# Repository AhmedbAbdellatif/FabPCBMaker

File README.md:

# FabPCBMaker
A fabbable, cheap, light and small CNC for PCBs

## Project Development
I developed this project as a final project for FabAcademy 2017. My idea was to make it possible to make a CNC mill for PCBs in a FabLab at an as low as possible cost (less than 100€). 
In this page I will be providing Information on how to replicate this along with the design files required  

## Specifications
* 100x160x50mm working area
* 0.0025mm theorethical resolution (0.04mm realistic)
* 18mm plywood cnc milled frame
* POM bearing and motor holder
* brushless spindle motor
* 3 x Pololu A4988
* 3 x Nema 17 threaded rod stepper motors
* 8mm linear rods
* satshakit board

## Thanks 
Daniele Ingrassia<br />
[Satshakit](https://github.com/satshakit)<br />

[FabLab Kamp-Lintfort](http://fablab.hochschule-rhein-waal.de/index.php/en/)<br />
[Hochschule Rhein-Waal](https://www.hochschule-rhein-waal.de/en)<br />
Friedrich-Heinrich-Allee 25, 47475 Kamp-Lintfort, Germany
fablab@hochschule-rhein-waal.de
## License
This work is licensed under the terms of Attribution-NonCommercial-ShareAlike 4.0 International ([CC BY-NC-SA 4.0](https://creativecommons.org/licenses/by-nc-sa/4.0/))

## Authors  
Ahmed B.Abdellatif<br />
Student Assistant at FabLab Kamp-Lintfort<br />
Communication and Information Engineering student Hochschule Rhein-Waal<br />

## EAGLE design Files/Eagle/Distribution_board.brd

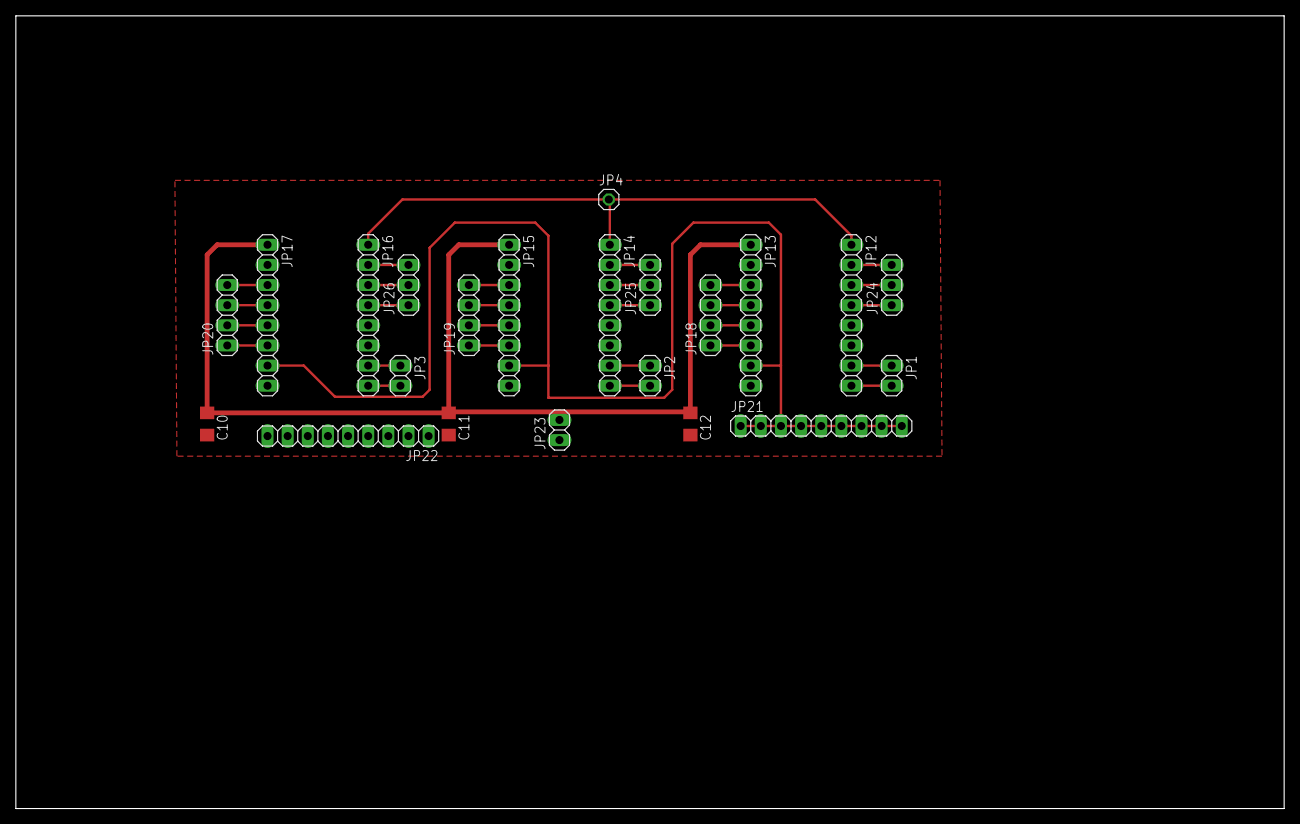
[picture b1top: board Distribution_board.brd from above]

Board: 2 copper layers, 160.0 x 100.0 mm, 22 parts (0 on the bottom side), 31 nets.

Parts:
C10, C11, C12: 100uF; C1206
JP1, JP2, JP3: 1X02
JP4: 1X01
JP12: X1; 1X08
JP13: X2; 1X08
JP14: Y1; 1X08
JP15: Y2; 1X08
JP16: Z1; 1X08
JP17: Z2; 1X08
JP18: Xout; 1X04
JP19: Yout; 1X04
JP20: Zout; 1X04
JP21, JP22: 1X09
JP23: MotorPW; 1X02
JP24, JP25, JP26: 1X03

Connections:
ENABLE: JP4.1, JP12.1, JP14.1, JP16.1
GND: C10.2, C11.2, C12.2, JP13.2, JP13.8, JP15.2, JP15.8, JP17.2, JP17.8, JP22.1, JP22.2, JP22.3, JP22.4, JP22.5, JP22.6, JP22.7, JP22.8, JP22.9, JP23.1
unnamed: JP17.3, JP20.4
unnamed: JP17.4, JP20.3
unnamed: JP17.5, JP20.2
unnamed: JP17.6, JP20.1
unnamed: JP15.6, JP19.1
unnamed: JP15.5, JP19.2
unnamed: JP15.4, JP19.3
unnamed: JP15.3, JP19.4
unnamed: JP13.3, JP18.4
unnamed: JP13.4, JP18.3
unnamed: JP13.5, JP18.2
unnamed: JP13.6, JP18.1
unnamed: JP12.2, JP24.3
unnamed: JP12.3, JP24.2
unnamed: JP12.4, JP24.1
unnamed: JP14.2, JP25.3
unnamed: JP14.3, JP25.2
unnamed: JP14.4, JP25.1
unnamed: JP16.2, JP26.3
unnamed: JP16.3, JP26.2
unnamed: JP16.4, JP26.1
VCC: JP13.7, JP15.7, JP17.7, JP21.1, JP21.2, JP21.3, JP21.4, JP21.5, JP21.6, JP21.7, JP21.8, JP21.9
VMOT: C10.1, C11.1, C12.1, JP13.1, JP15.1, JP17.1, JP23.2
XDIR: JP1.2, JP12.8
XSTEP: JP1.1, JP12.7
YDIR: JP2.2, JP14.8
YSTEP: JP2.1, JP14.7
ZDIR: JP3.2, JP16.8
ZSTEP: JP3.1, JP16.7

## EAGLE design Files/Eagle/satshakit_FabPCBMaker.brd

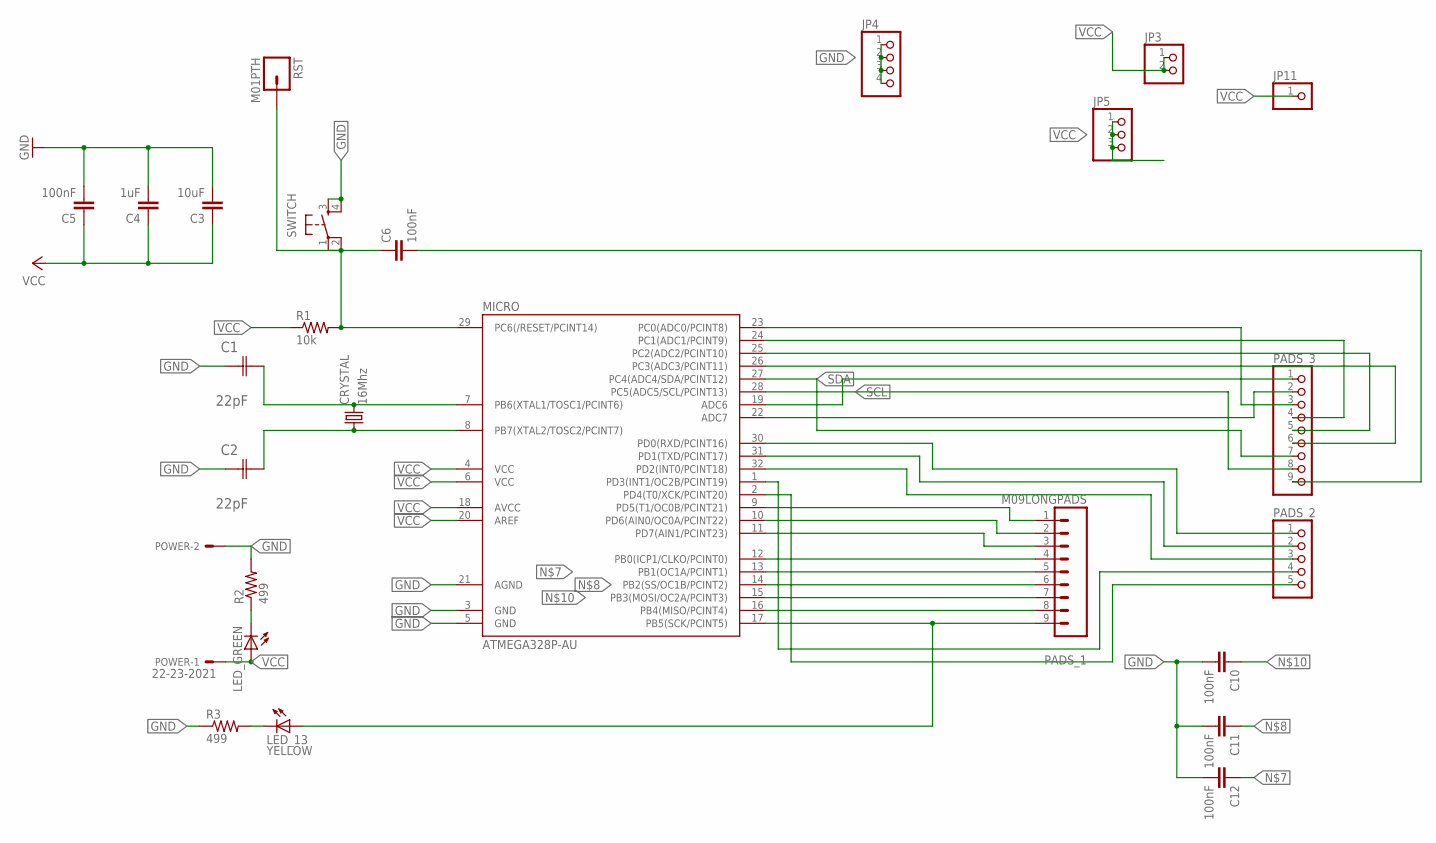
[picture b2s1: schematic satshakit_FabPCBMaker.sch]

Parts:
C1, C2: 22pF; CAPC3216X178N
C3: 10uF; 1206
C4: 1uF; 1206
C5, C6, C10, C11, C12: 100nF; 1206
CRYSTAL: 16Mhz; CSM-7X-DU
JP3: PINHD-1X2; 1X02
JP4: PINHD-1X4; 1X04
JP5: PINHD-1X3; 1X03
JP11: PINHD-1X1; 1X01
LED_13: YELLOW; 1206
LED_GREEN: LED1206; 1206
MICRO: ATMEGA328P-AU; TQFP32-08
PADS_1: M09LONGPADS; 1X09_LONGPADS
PADS_2: PINHD-1X5; 1X05
PADS_3: PINHD-1X9; 1X09
POWER: 22-23-2021
R1: 10k; 1206
R2, R3: 499; 1206
RST: M01PTH; 1X01
SWITCH: 6MM_SWITCH6MM_SWITCH; 6MM_SWITCH

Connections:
GND: C1.1 (C1), C2.1 (C1), C3.2, C4.2, C5.2, C10.2, C11.2, C12.2, JP4.1, JP4.2, JP4.3, JP4.4, MICRO.3 (GND), MICRO.5 (GND), MICRO.21 (AGND), POWER.2, R2.2, R3.1, SWITCH.3 (S), SWITCH.4 (S1)
unnamed: MICRO.9 (PD5(T1/OC0B/PCINT21)), PADS_1.1
unnamed: C1.2 (C2), CRYSTAL.2, MICRO.7 (PB6(XTAL1/TOSC1/PCINT6))
unnamed: C6.2, PADS_3.9
unnamed: MICRO.10 (PD6(AIN0/OC0A/PCINT22)), PADS_1.2
unnamed: MICRO.11 (PD7(AIN1/PCINT23)), PADS_1.3
unnamed: MICRO.12 (PB0(ICP1/CLKO/PCINT0)), PADS_1.4
unnamed: C12.1, MICRO.13 (PB1(OC1A/PCINT1)), PADS_1.5
unnamed: C11.1, MICRO.14 (PB2(SS/OC1B/PCINT2)), PADS_1.6
unnamed: C2.2 (C2), CRYSTAL.1, MICRO.8 (PB7(XTAL2/TOSC2/PCINT7))
unnamed: C10.1, MICRO.15 (PB3(MOSI/OC2A/PCINT3)), PADS_1.7
unnamed: MICRO.16 (PB4(MISO/PCINT4)), PADS_1.8
unnamed: LED_13.1 (A), MICRO.17 (PB5(SCK/PCINT5)), PADS_1.9
unnamed: MICRO.19 (ADC6), PADS_3.1
unnamed: MICRO.22 (ADC7), PADS_3.2
unnamed: MICRO.23 (PC0(ADC0/PCINT8)), PADS_3.3
unnamed: MICRO.24 (PC1(ADC1/PCINT9)), PADS_3.4
unnamed: MICRO.25 (PC2(ADC2/PCINT10)), PADS_3.5
unnamed: MICRO.26 (PC3(ADC3/PCINT11)), PADS_3.6
unnamed: MICRO.30 (PD0(RXD/PCINT16)), PADS_2.1
unnamed: MICRO.31 (PD1(TXD/PCINT17)), PADS_2.2
unnamed: MICRO.32 (PD2(INT0/PCINT18)), PADS_2.3
unnamed: MICRO.1 (PD3(INT1/OC2B/PCINT19)), PADS_2.4
unnamed: MICRO.2 (PD4(T0/XCK/PCINT20)), PADS_2.5
unnamed: LED_GREEN.2 (C), R2.1
unnamed: LED_13.2 (C), R3.2
unnamed: C6.1, MICRO.29 (PC6(/RESET/PCINT14)), R1.2, RST.1, SWITCH.1, SWITCH.2 (P1)
SCL: MICRO.28 (PC5(ADC5/SCL/PCINT13)), PADS_3.8
SDA: MICRO.27 (PC4(ADC4/SDA/PCINT12)), PADS_3.7
VCC: C3.1, C4.1, C5.1, JP3.1, JP3.2, JP5.1, JP5.2, JP5.3, JP11.1, LED_GREEN.1 (A), MICRO.4 (VCC), MICRO.6 (VCC), MICRO.18 (AVCC), MICRO.20 (AREF), POWER.1, R1.1

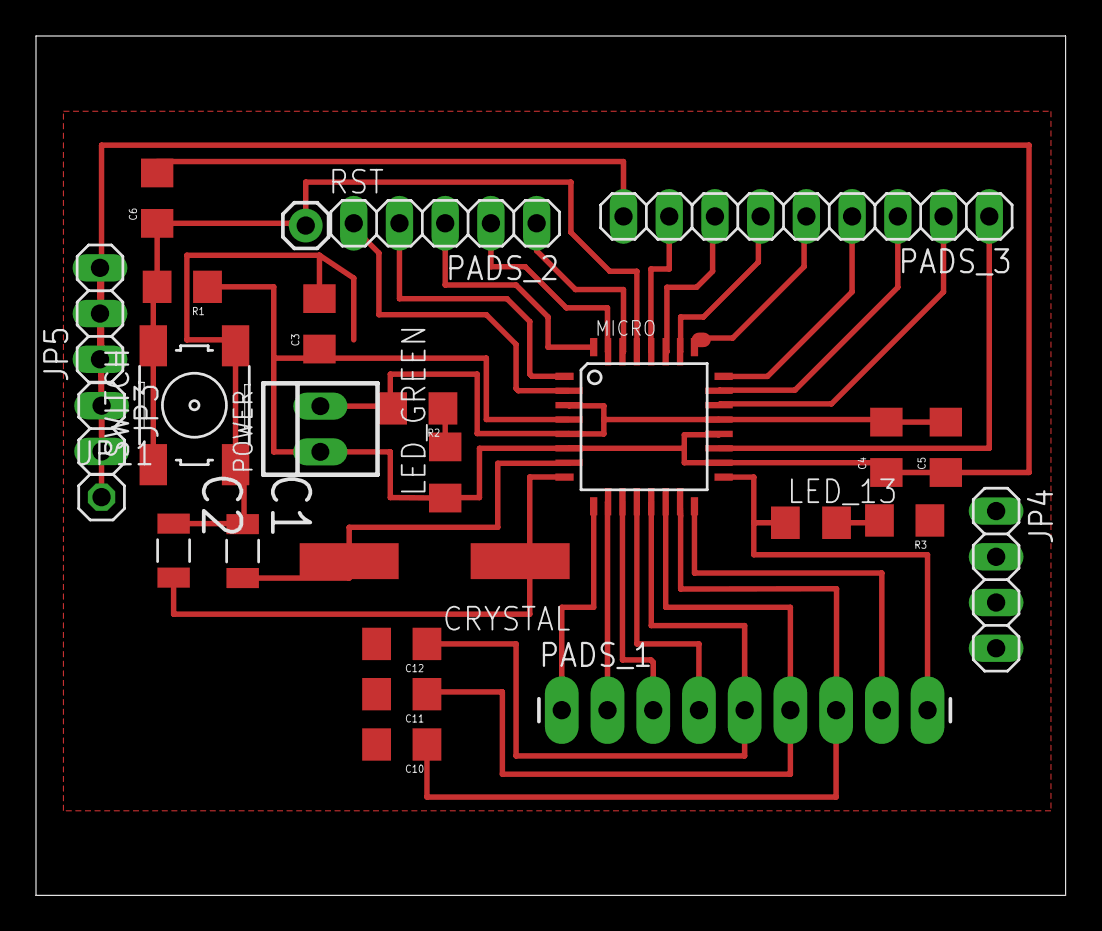
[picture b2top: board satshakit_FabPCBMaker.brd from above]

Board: 2 copper layers, 57.2 x 47.7 mm, 26 parts (0 on the bottom side), 30 nets.

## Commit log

2017-06-21 License
2017-06-21 Files
2017-06-21 Specs Added
2017-06-21 Organised

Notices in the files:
parts and their libraries:
01_SparkFun: Licensing: CC v3.0 Share-Alike You are welcome to use this library for commercial purposes.
